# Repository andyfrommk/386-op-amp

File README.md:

TODO:
Seperate labeled pins for voltage in and ground? danger of getting it wrong although the square marked pin headers are all grounds.
Make sure those pots we have match the holes on the board before commiting to fab house.
Add option to surface mount decoupling cap onto pin 7?  
Spread out components and add labels to make a soldering kit (50mmx50mm board) otherwise this 32mmx32mm board should suffice.

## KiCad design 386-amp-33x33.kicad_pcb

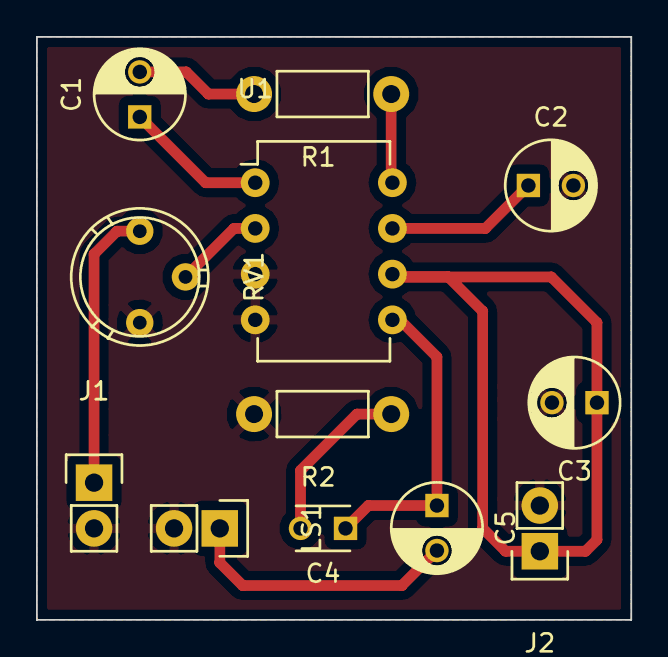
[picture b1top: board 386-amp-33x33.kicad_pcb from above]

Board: 2 copper layers, 33.0 x 32.4 mm, 12 parts (0 on the bottom side), 11 nets.

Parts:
C1, C2: 22u; C_Radial_D5_L6_P2.5
C3, C5: 220u; C_Radial_D5_L6_P2.5
C4: 0u1; C_Disc_D3_P2.5
J1: INPUT; Pin_Header_Straight_1x02
J2: VCC; Pin_Header_Straight_1x02
LS1: Speaker; Pin_Header_Straight_1x02
R1: 1K2; Resistor_Horizontal_RM7mm
R2: 10R; Resistor_Horizontal_RM7mm
RV1: 10K; Potentiometer_Bourns_3339P_Angular_ScrewUp
U1: LM386; DIP-8_W7.62mm

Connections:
+12V: C3.1, J2.1, U1.6
GND: C2.2, C3.2, J1.2, J2.2, LS1.2, R2.2, RV1.3, U1.3, U1.4
unnamed: C1.1, U1.1
unnamed: C1.2, R1.2
unnamed: C2.1, U1.7
unnamed: C4.1, C5.1, U1.5
unnamed: C4.2, R2.1
unnamed: C5.2, LS1.1
unnamed: J1.1, RV1.1
unnamed: R1.1, U1.8
unnamed: RV1.2, U1.2

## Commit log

2017-09-10 getting there
